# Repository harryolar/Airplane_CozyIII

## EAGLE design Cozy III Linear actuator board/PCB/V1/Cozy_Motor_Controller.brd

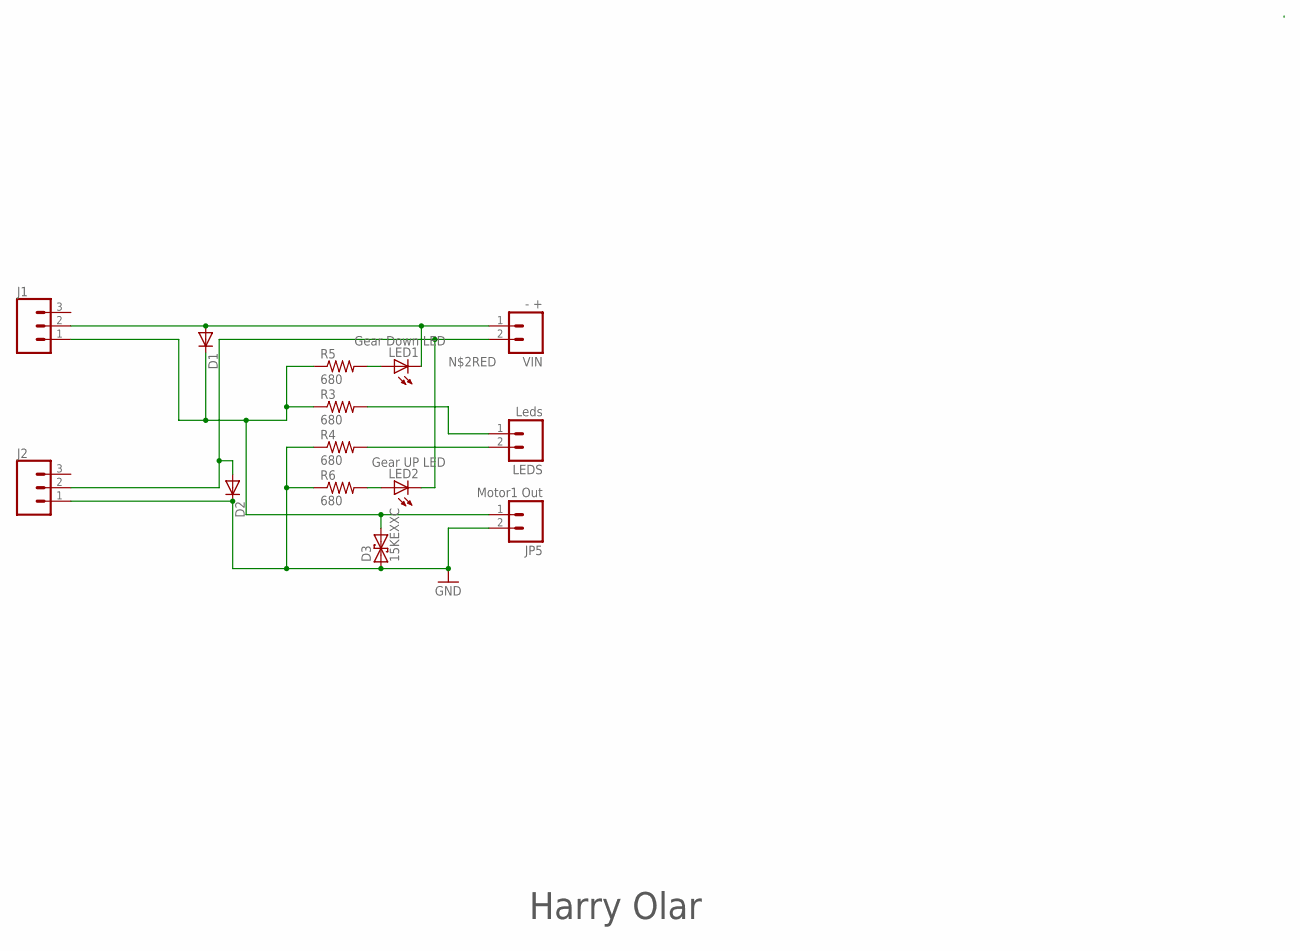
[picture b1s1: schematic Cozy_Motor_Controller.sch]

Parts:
D1, D2: DIODE-C221B1A; C221B1A
D3: 15KEXXC; CB429-17
J1, J2: CONN_03-SCREW-5MM; SCREWTERMINAL-5MM-3
JP5: Motor1 Out; SCREWTERMINAL-5MM-2
LED1: Gear Down LED; LED3MM
LED2: Gear UP LED; LED3MM
LEDS: Leds; SCREWTERMINAL-5MM-2
R3, R4, R5, R6: 680; R0805
VIN: - +; SCREWTERMINAL-5MM-2

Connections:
GND: D2.C, D3.A (1), J2.1, JP5.2, R4.1, R6.1
unnamed: LEDS.1, R3.2
unnamed: LEDS.2, R4.2
unnamed: D1.A, J1.2, LED1.K (C), VIN.1
unnamed: D2.A, J2.2, LED2.K (C), VIN.2
unnamed: D1.C, D3.C (2), J1.1, JP5.1, R3.1, R5.1
unnamed: LED2.A, R6.2
unnamed: LED1.A, R5.2

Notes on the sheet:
Harry Olar

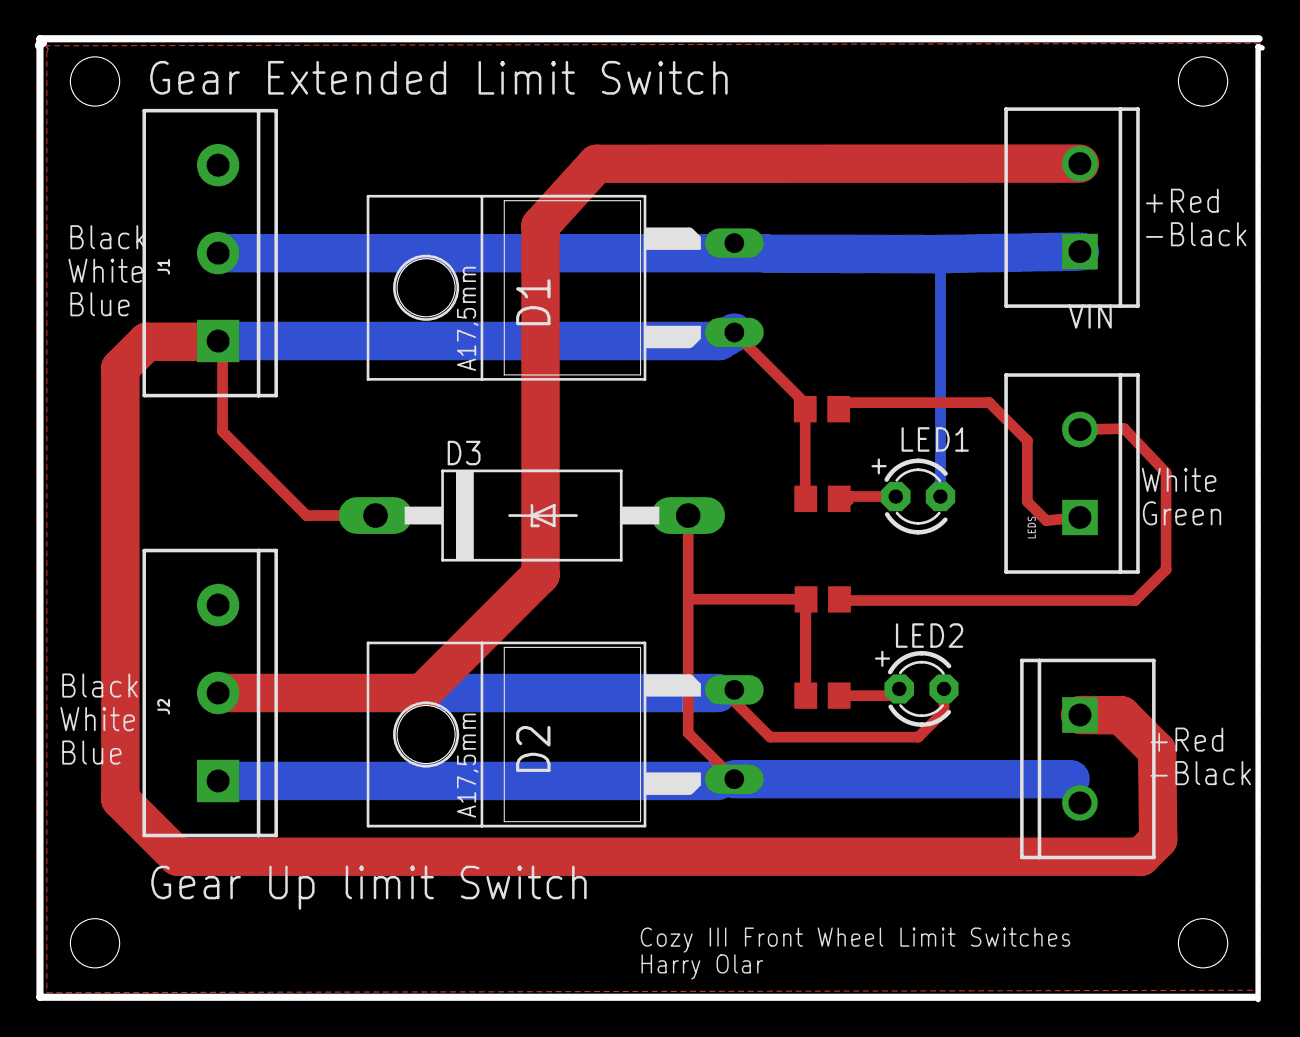
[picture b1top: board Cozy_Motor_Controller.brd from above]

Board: 2 copper layers, 69.5 x 54.6 mm, 14 parts (0 on the bottom side), 8 nets.

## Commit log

2022-08-10 added the flight stick and the front wheel actuator board
2022-08-10 added images
    added images

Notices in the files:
parts and their libraries:
SparkFun-Connectors: Licensing: CC v3.0 Share-Alike You are welcome to use this library for commercial purposes.
